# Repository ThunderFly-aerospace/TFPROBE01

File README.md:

# TFPROBE01A - Omnipolar magnetic and reflective optical sensor probe

The sensor is designed for RPM measurement with [TFRPM01 sensor board](https://github.com/ThunderFly-aerospace/TFRPM01). The probe consists dual sensing technique - optical or magnetic. Therefore the user should select the one most suitable for the application.

> This device was developed by [ThunderFly s.r.o.](https://www.thunderfly.cz) and is published as OpenSource hardware with a [GPLv3](LICENSE) license. It is commercially available, for a quote contact us by email at info@thunderfly.cz. Or buy it directly together with a [TFRPM01](https://docs.thunderfly.cz/avionics/TFRPM01/) sensor at [Tindie store](https://www.tindie.com/products/thunderfly/tfrpm01-drone-rpm-tachometer-sensor/).

### Magnetic Sensing

The magnetic Hall-effect sensor mounted on the probe board can sense both directions of the magnetic field. The strength of the magnetic field is a decisive parameter for the probe's correct function. The magnetic flux is expected to be perpendicular to the sensor PCB surface. The detailed requirements of magnetic flux density are described in [AH3572 datasheet page 4](/doc/datasheets/AH3572-1483253.pdf).

In magnetic sensing, it is recommended to cover the probe in a black shrinking tube.  The covering blocks function of a reflective sensor.

### Optical Sensing

An optical sensor is sensitive to the infrared reflectance of material (usually a rotating disc with marks).
To details see the [VCNT2020 datasheet page 2](/doc/datasheets/vcnt2020.pdf)

## Hardware
TFPROBE01A is designed as Open-Hardware (GPL v3). All documentation is located in this repository.

The TFPROBE01 is sold and shipped without a soldered header, because its orientation may depend on the customer's use. Connecting cable and two headers (one straight and one right-angled) are included.

### PCB

#### PCB dimensions

##### Optical and magnetic probe positions on PCB

### Electronic schema

Full schema is available in [PDF](/doc/gen/TFPROBE01A-schematic.pdf)

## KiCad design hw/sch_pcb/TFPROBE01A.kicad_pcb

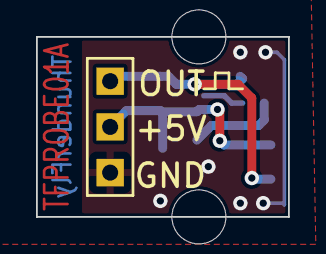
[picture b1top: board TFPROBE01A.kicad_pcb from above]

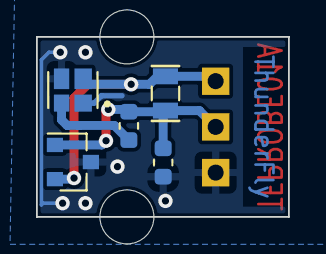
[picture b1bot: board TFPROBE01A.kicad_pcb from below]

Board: 2 copper layers, 14.0 x 10.0 mm, 8 parts (5 on the bottom side), 4 nets.

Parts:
C1: 100nF; SMD-0603
J1: HEADER_1x03; Straight_1x03
M3, M4: HOLE; dira_3mm
R1: 180R; SMD-0603
R2: -; SMD-0805
U1: AH3572; SOT-23
U2: VCNT2020; XDCR_VCNT2020

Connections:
+5V: C1.1, J1.2, R1.1, R2.1, U1.1 (VDD)
/COUNT: J1.1, R2.2, U1.2 (OUT), U2.2
GND: C1.2, J1.3, U1.3 (GND), U2.1, U2.4
unnamed: R1.2, U2.3

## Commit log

2020-10-26 Schema
2020-10-29 Edit
2020-10-29 Create LICENSE
2020-10-30 Edit 3D images
2020-10-30 Edit images
2020-10-30 3D images
2020-10-30 Rename
2020-10-30 Crop images and design check.
2020-10-31 Edit bom
2020-11-01 Přejmenování modulu. Generování výrobních dat.
2020-11-01 Odstranění starých dat.
2020-11-01 Přidány kóty.
2020-11-04 Edit cam
2020-11-12 Vložení souborů pro automatické generování schéma.
2020-11-12 Edit schema
2020-11-12 Automation
2020-11-20 Flip pin-header connector to opposite side. #3
2020-11-20 add datasheets.
2020-11-25 Schematic export.
2021-01-23 Update title block.
2021-02-22 Improve documentation, images and automation.
2021-02-22 Fix wrog link to images.
2021-02-23 uprava obrazku, pridani obrazku baleni
2021-04-03 Changing component values #5
2021-04-05 Improve the schematics title blocks.
2021-04-05 Replotting the schema.
2021-04-07 Update documentation regarding the dimensions of the PCB.
2021-04-07 Improve readme.
2021-08-09 Add dimensions to optical probe sensor.
2022-10-18 Edit PCB
2022-10-18 Edid workflows
2022-10-18 Update actions products
2023-08-10 Update README.md
    check the spelling
    add a link to the optical sensor datasheet.
2023-08-12 Update sensors position dimensions
2024-03-26 Update README.md
    Update link to documentation.
2025-03-05 Actual Tindie listing.
2025-03-05 Update product listing.
